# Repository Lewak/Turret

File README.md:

# INSTRUKCJA
## vol.1 RASPBERRY JAKO ETHERNET GADGET
1. Podłączyć raspberry za pomocą kabla USB (DO PORTU USBIN nie USB POWER!)
2. Sprawdzić w menadżerze urządzeń czy jest wykrywany jako usb ethernet gadget. Jak tak, przejść do kroku 6
3. Pobrać sterownik usb ethernet gadget (Acer Incorporated. - Other hardware - USB Ethernet/RNDIS Gadget) stąd: 
	https://www.catalog.update.microsoft.com/Search.aspx?q=USB%20RNDIS%20Gadget
4. Wypakować pobrane archiwum, kliknąć ppm na RNDIS.inf i wybrać install
5. Wejść w menadżer urządzeń, odłączyć i podłączyć RPi, żeby zobaczyć jako co jest wykrywane - może to być np. port COM. Wybrać to urządzenie, 
	update driver, browse my computer, let me pick from a list.., have disk, wybrać RNDIS.inf. Sprawdzić czy teraz jest wykrywany, 
	jak nie to można się popłakać i zawołać mazura.
6. Spróbować połączyć się za pomocą komendy ssh, adres IP można zdobyć poprzez ipconfig albo spróbować użyć: ssh pi@raspberrypi.local (hasło to raspberry)
7. Mozna zainstalowac sterownik Bonjour, by moc używać nazwy .local w IDE (możliwe że niepotrzebne)
8. By uruchomić internet na raspberry. Należy wejść w windows panel sterownia, network and sharing -> change adapter settings
	(old: ethernet settings -> change adapter settings) 
	wybrać AKTUALNE DZIAŁAJĄCE POŁĄCZENIE INTERNETOWE (NIE IP RASPBERRY) -> properties -> settings ->sharing -> w obu checkboxach zaznaczyć allow 
	i wybrać Ethernet gadget RPi
9. Powinno działać 

## vol.2 DŹWIĘK I IO
1. Plik do dźwięku znajduje sie w: /etc/asound.conf
2. Plik autostartu z komendami uruchamianymi przy boocie to /etc/rc.local (komenda sudo pigpiod -t 0)
		
## vol.3 PROCEDURA URUCHAMIANIA TURRETA
1. Wpisać login i password w deployment w file->settings->deployment: login:pi hasło: raspberry
2. Prawy przycisk na pliki programu i deployment->send to raspberrypi
3. Jak jest problem z serial permission denied: sudo chmod 666 /dev/ttyAMA0

## vol.4 PROCEDURA URUCHAMIANIA PŁYKI ENDERA
1. Zainstalować środowisko kombatybilne z Arduino (np Visual Studio Code z pluginem). 
2. Zainstalować boardy Sanguino
3. Przed uploadem ustawić port COM, ustawić płytkę Sanguino z procesorem Atmega1284 16Mhz.

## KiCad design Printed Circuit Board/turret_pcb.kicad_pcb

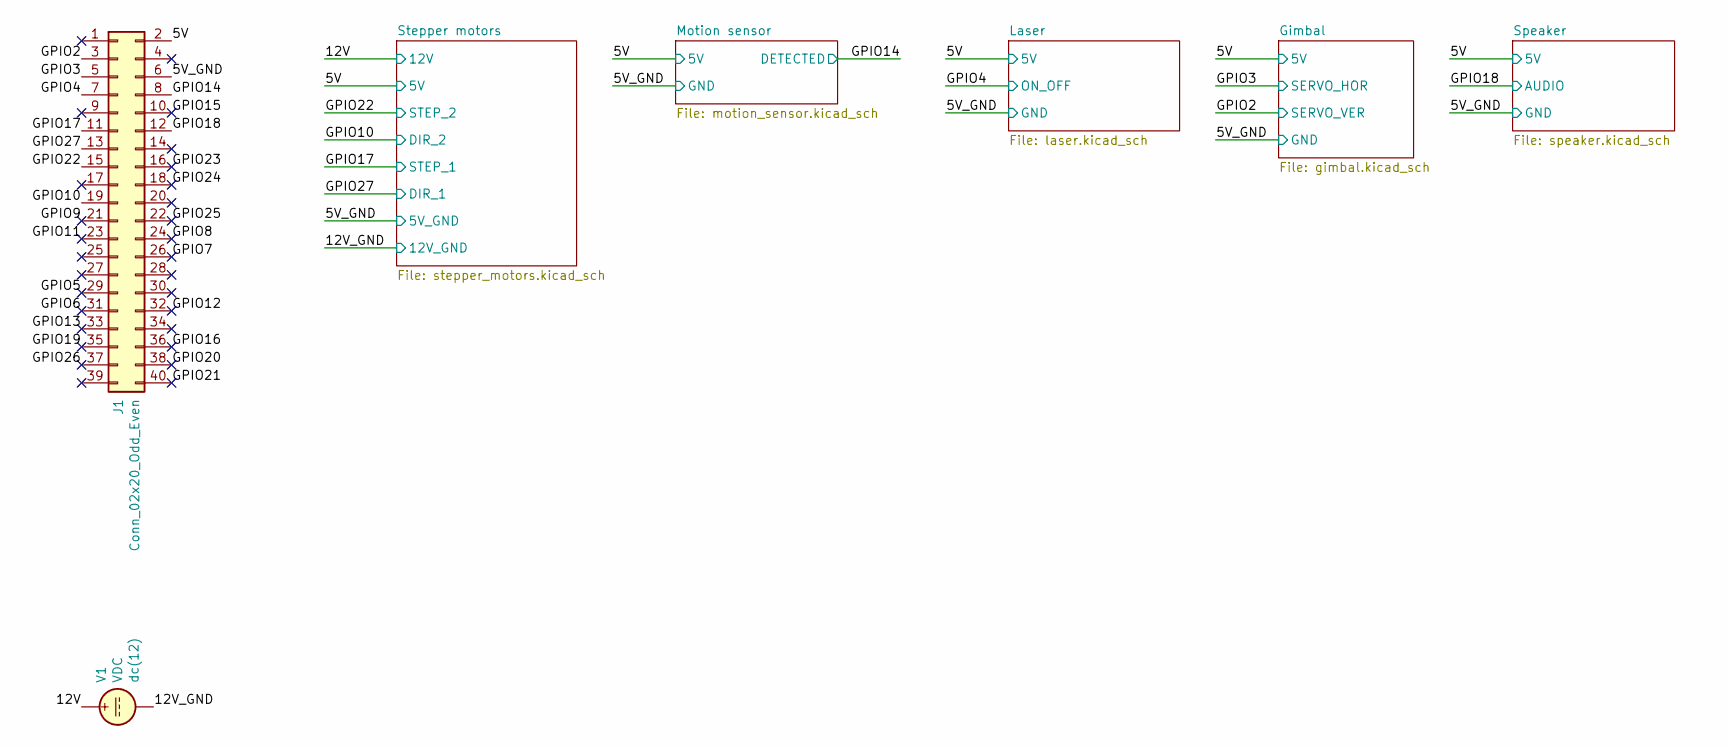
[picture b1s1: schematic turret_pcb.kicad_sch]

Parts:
J1: Conn_02x20_Odd_Even; PinSocket_2x20_P2.54mm_Vertical
V1: VDC; Banana_Jack_2Pin

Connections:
/5V: J1.2; also elsewhere on the board
/5V_GND: J1.6; also elsewhere on the board
/12V: V1.1; also elsewhere on the board
/12V_GND: V1.2; also elsewhere on the board
/GPIO2: J1.3; also elsewhere on the board
/GPIO3: J1.5; also elsewhere on the board
/GPIO4: J1.7; also elsewhere on the board
/GPIO5: J1.29
/GPIO6: J1.31
/GPIO7: J1.26
/GPIO8: J1.24
/GPIO9: J1.21
/GPIO10: J1.19; also elsewhere on the board
/GPIO11: J1.23
/GPIO12: J1.32
/GPIO13: J1.33
/GPIO14: J1.8; also elsewhere on the board
/GPIO15: J1.10
/GPIO16: J1.36
/GPIO17: J1.11; also elsewhere on the board
/GPIO18: J1.12; also elsewhere on the board
/GPIO19: J1.35
/GPIO20: J1.38
/GPIO21: J1.40
/GPIO22: J1.15; also elsewhere on the board
/GPIO23: J1.16
/GPIO24: J1.18
/GPIO25: J1.22
/GPIO26: J1.37
/GPIO27: J1.13; also elsewhere on the board

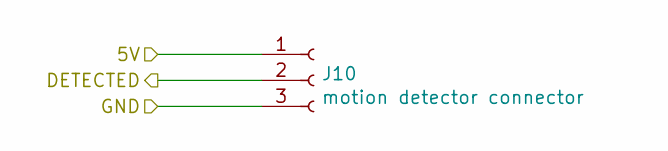
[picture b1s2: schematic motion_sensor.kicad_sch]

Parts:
J10: motion detector connector; PinHeader_1x03_P2.54mm_Vertical

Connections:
/5V: J10.1; also elsewhere on the board
/5V_GND: J10.3; also elsewhere on the board
/GPIO14: J10.2; also elsewhere on the board

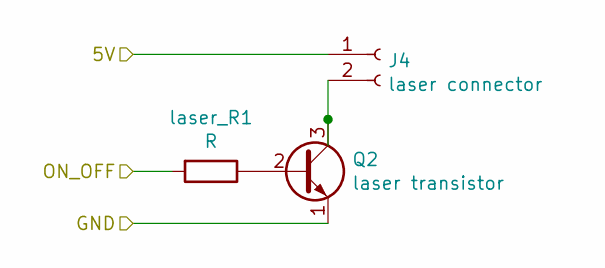
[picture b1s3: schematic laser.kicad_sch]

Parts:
J4: laser connector; PinHeader_1x02_P2.54mm_Vertical
Q2: laser transistor; TO-39-3
laser_R1: R; R_1206_3216Metric

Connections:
/5V: J4.1; also elsewhere on the board
/5V_GND: Q2.1 (E); also elsewhere on the board
/GPIO4: laser_R1.2; also elsewhere on the board
unnamed: J4.2, Q2.3 (C)
unnamed: Q2.2 (B), laser_R1.1

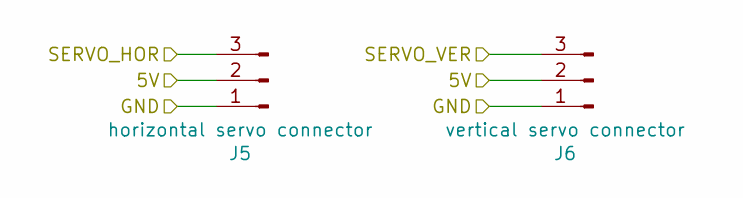
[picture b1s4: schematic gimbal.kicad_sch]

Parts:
J5: horizontal servo connector; PinHeader_1x03_P2.54mm_Vertical
J6: vertical servo connector; PinHeader_1x03_P2.54mm_Vertical

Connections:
/5V: J5.2, J6.2; also elsewhere on the board
/5V_GND: J5.1, J6.1; also elsewhere on the board
/GPIO2: J6.3; also elsewhere on the board
/GPIO3: J5.3; also elsewhere on the board

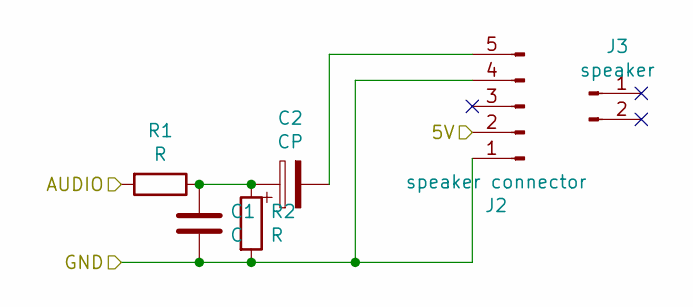
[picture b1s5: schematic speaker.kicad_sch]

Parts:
C1: C; C_Disc_D4.7mm_W2.5mm_P5.00mm
C2: CP; C_Radial_D6.3mm_H5.0mm_P2.50mm
J2: speaker connector; PinHeader_1x05_P2.54mm_Vertical
J3: speaker; PinHeader_1x02_P2.54mm_Vertical
R1: R; R_1206_3216Metric_Pad1.30x1.75mm_HandSolder
R2: R; R_1206_3216Metric

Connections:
/5V: J2.2; also elsewhere on the board
/5V_GND: C1.2, J2.1, J2.4, R2.2; also elsewhere on the board
/GPIO18: R1.2; also elsewhere on the board
unnamed: C1.1, C2.1, R1.1, R2.1
unnamed: C2.2, J2.5

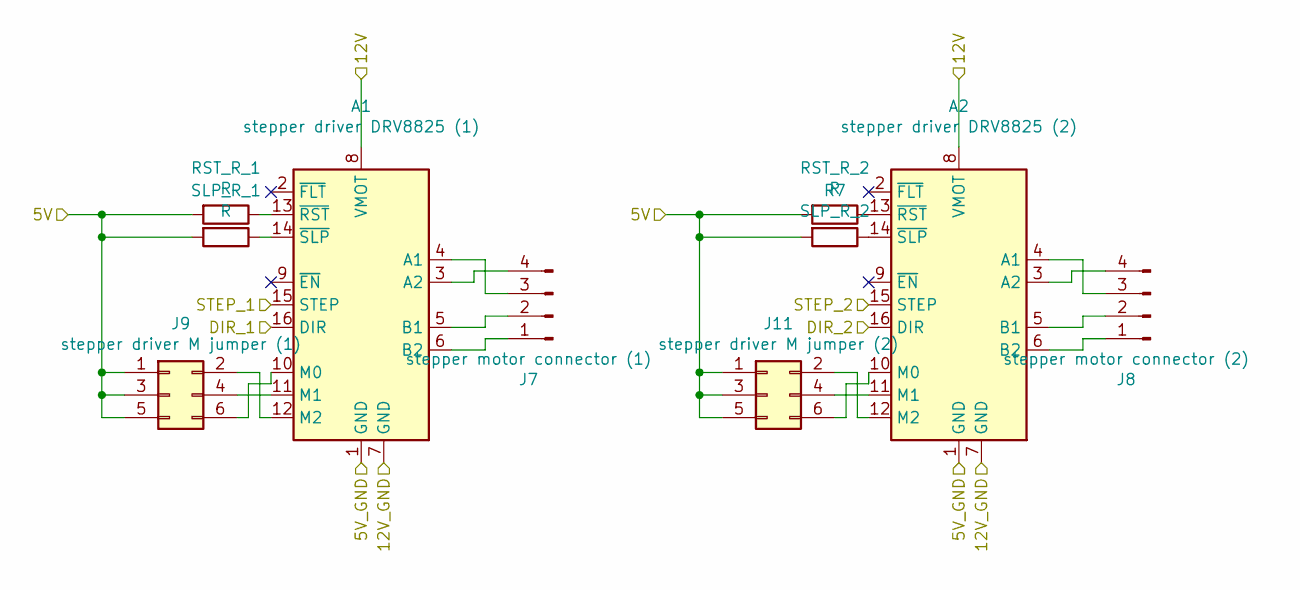
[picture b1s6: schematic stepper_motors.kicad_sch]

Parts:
A1: stepper driver DRV8825 (1); Pololu_Breakout-16_15.2x20.3mm
A2: stepper driver DRV8825 (2); Pololu_Breakout-16_15.2x20.3mm
J7: stepper motor connector (1); PinHeader_1x04_P2.54mm_Vertical
J8: stepper motor connector (2); PinHeader_1x04_P2.54mm_Vertical
J9: stepper driver M jumper (1); PinSocket_2x03_P2.54mm_Vertical
J11: stepper driver M jumper (2); PinSocket_2x03_P2.54mm_Vertical
R7: SLP_R_2; R_1206_3216Metric
RST_R_1, RST_R_2: R; R_1206_3216Metric
SLP_R_1: R; R_1206_3216Metric

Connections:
/5V: J9.1, J9.3, J9.5, J11.1, J11.3, J11.5, R7.2, RST_R_1.2, RST_R_2.2, SLP_R_1.2; also elsewhere on the board
/5V_GND: A1.1 (GND), A2.1 (GND); also elsewhere on the board
/12V: A1.8 (VMOT), A2.8 (VMOT); also elsewhere on the board
/12V_GND: A1.7 (GND), A2.7 (GND); also elsewhere on the board
/GPIO10: A2.16 (DIR); also elsewhere on the board
/GPIO17: A1.15 (STEP); also elsewhere on the board
/GPIO22: A2.15 (STEP); also elsewhere on the board
/GPIO27: A1.16 (DIR); also elsewhere on the board
unnamed: A1.3 (A2), J7.4
unnamed: A1.4 (A1), J7.3
unnamed: A1.5 (B1), J7.2
unnamed: A1.6 (B2), J7.1
unnamed: A1.10 (M0), J9.6
unnamed: A1.11 (M1), J9.4
unnamed: A1.12 (M2), J9.2
unnamed: A1.13 (~RST), RST_R_1.1
unnamed: A1.14 (~SLP), SLP_R_1.1
unnamed: A2.3 (A2), J8.4
unnamed: A2.4 (A1), J8.3
unnamed: A2.5 (B1), J8.2
unnamed: A2.6 (B2), J8.1
unnamed: A2.10 (M0), J11.6
unnamed: A2.11 (M1), J11.4
unnamed: A2.12 (M2), J11.2
unnamed: A2.13 (~RST), RST_R_2.1
unnamed: A2.14 (~SLP), R7.1

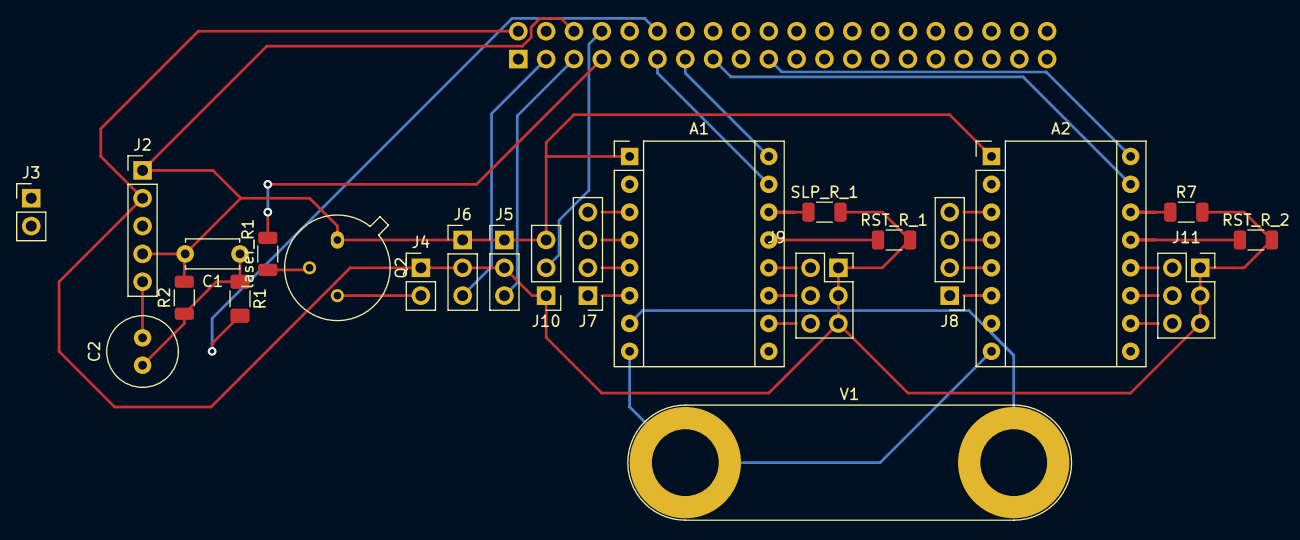
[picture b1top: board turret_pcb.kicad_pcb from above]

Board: 2 copper layers, 24 parts (1 on the bottom side), 35 nets.

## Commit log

2020-07-22 gowno
2020-07-22 clean test, test2
2020-07-25 Laser class completed. Added clause to turn it off at the end of execution
2020-07-25 Servo and Gimbal class completed
2020-07-26 Updated type references
2020-07-29 Repo structure change
2020-08-04 random_path_generator added
2020-08-04 path generator visualisation test
2020-08-04 audio samples
2020-08-04 Added parts used in testing phase
2020-08-06 Added some new exciting features, Added GPIOinterface and motion sensor
2020-08-06 pinout image
2020-08-06 consistent typing and spacing
2020-08-07 costs.xlsx
2020-08-07 Added sound support.
2020-08-07 Ignoring some files
2020-08-31 Audio interface refactor & costs
2020-10-06 Inventor turret assembly
2020-10-09 Turret main mechanism upgrade
2020-10-10 Main mechanism decomposition
2020-10-10 assembly fix
2020-10-12 main_stand_upper_half loft fixed
2020-10-21 Lower stand fixed. Added STL models to print
2020-10-21 Lowered the ammount of PLA used.
2020-10-23 Swash distance added, fixed bearing mount
2020-10-24 Trying hard to write state machine pattern
2020-10-24 actuators holders
2020-10-26 Models improvements, assembly constraints fixed
2020-10-27 small fixes in models
2020-10-27 First implemented and working state machine.
    Some things to reconsider and/or change
2020-10-29 assembly in blueprint
2020-11-01 collinear actuator holders
2020-11-03 Błąd Gruby
2020-11-04 models small fixes
2020-11-14 costs
2020-11-14 Just lost 1 hour of code because of detached head (Not sure if mine, or git's). Anyway, here it is, written again. Something about splitting code.
2021-01-06 Wobble
2021-02-05 costs update
2021-02-09 The costs are piling up
2021-02-09 Improved searching and random aiming routine
2021-02-09 4.7 sekundy jest najlepszą jednostką czasu
2021-02-17 pneumatic costs
2021-02-18 PCB scheme only
2021-02-20 PCB separate schemas for components
2021-02-20 PCB: using m0, m1, m2 in stepper motors
2021-02-21 PCB: physical board prototype
2021-02-22 PCB physical board
2021-03-06 Adapted Pigpio library to control logic GPIO functions
2021-03-06 Added first power button implementation
2021-04-11 Nobody will ever read that, because it's failed branch. Never come here
2021-06-27 mini refactor
2021-06-27 cleaning code
2021-06-27 Added instruction file for utter morons.
2021-06-27 Added a lot of TODOS
2021-06-27 robotronik costs
2021-08-28 First version of Arduino side board program
2022-02-13 EnderLogic WIP
2022-02-13 Mazur jest bogiem
2022-02-13 refaktoryzacja kodu
2022-02-20 Added description about pins used for audio speaker
2022-04-28 KiCAD version updated 5 -> 6
2022-07-10 Update instruction for Raspberry Pi SSH connection
2022-07-10 Add laser part number to costs files
2022-12-10 Project cleanup
2022-12-11 Informational and organizational update
2023-01-15 project structure cleanup
2023-01-27 Gears ratio calculations
2023-02-11 ESP board initial setup
2023-02-11 working initial setup for esp + drv8825 + nema 17
2023-03-18 initial protocol setup for ESP
2023-05-28 Continuing working on C++ ESP32 code for motor driving.
2023-07-02 improvements and cleanup for assembly
2023-07-30 WIP: Inventor models for hal holders
2023-09-17 HAL sensors holders added to assembly
2024-02-11 Succesful connection between RsPI and ESP device. First implementation of stepper motor movement in gimbal achieved.
2025-05-26 commit after a year with i dont know what
